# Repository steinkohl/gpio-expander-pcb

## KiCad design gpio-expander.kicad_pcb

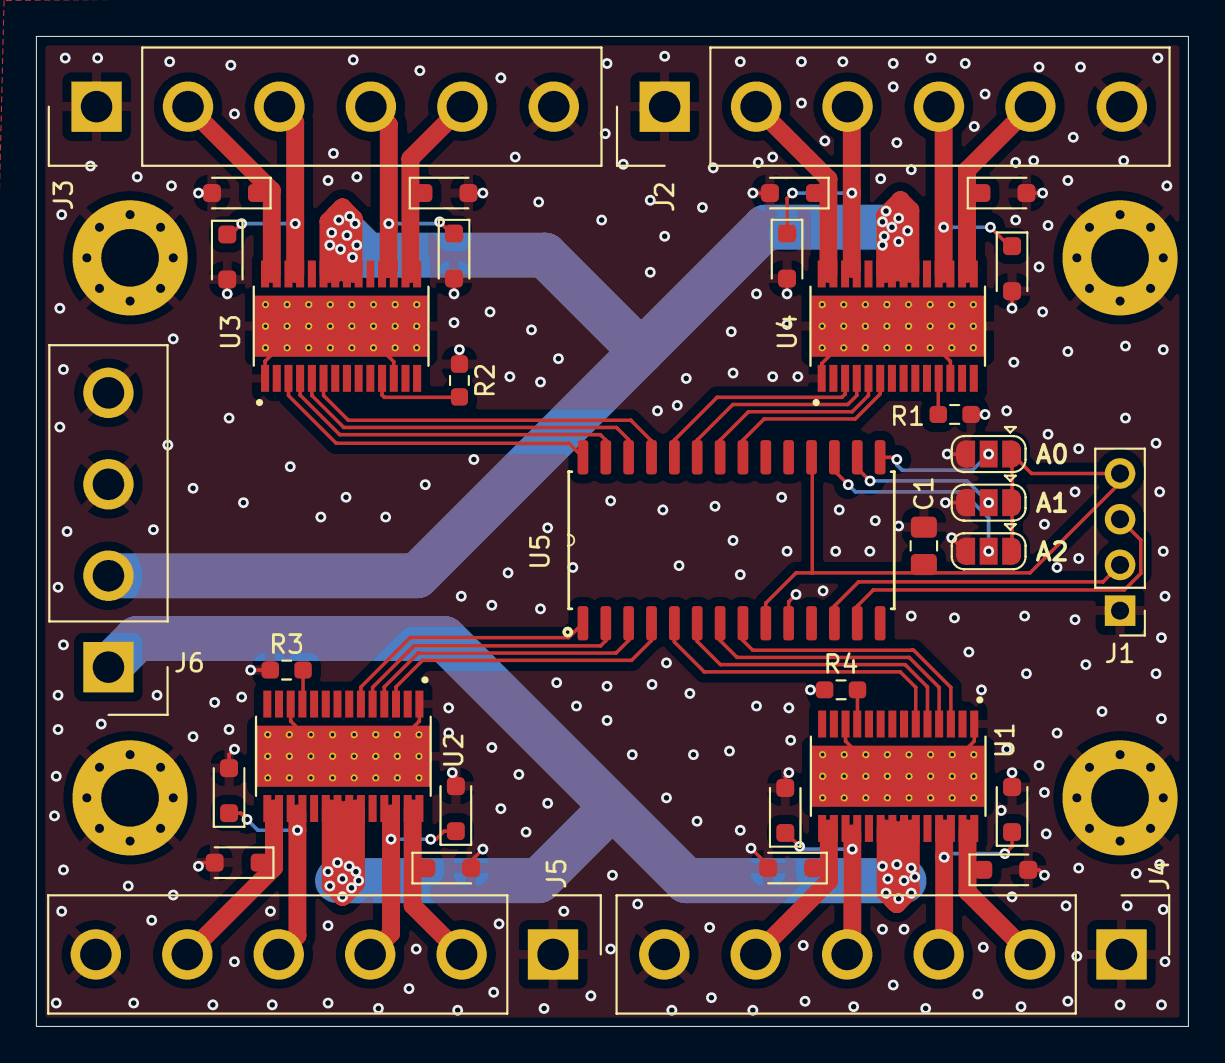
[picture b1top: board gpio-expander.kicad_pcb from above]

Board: 2 copper layers, 64.0 x 55.0 mm, 39 parts (0 on the bottom side), 44 nets.

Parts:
C1: C; C_0805_2012Metric_Pad1.18x1.45mm_HandSolder
D1, D2, D3, D4, D5, D6, D7, D8, D9, D10, D11, D12, D13, D14, D15, D16: 60V 1A; D_SOD-323_HandSoldering
H1, H2, H3, H4: MountingHole_Pad; MountingHole_3.2mm_M3_Pad_Via
J1: Conn_01x04; PinHeader_1x04_P2.54mm_Vertical
J2, J3, J4, J5: Conn_01x06; Samtec_HPM-06-05-x-S_Straight_1x06_Pitch5.08mm
J6: Conn_01x04; Samtec_HPM-04-05-x-S_Straight_1x04_Pitch5.08mm
JP1, JP2, JP3: SolderJumper_3_Open; SolderJumper-3_P1.3mm_Open_RoundedPad1.0x1.5mm
R1, R2, R3, R4: R; R_0603_1608Metric_Pad0.98x0.95mm_HandSolder
U1, U2, U3, U4: TPS4H160AQPWPRQ1; IC_TPS4H160AQPWPRQ1
U5: MCP23017T-E_SO; SOIC127P1030X265-28N

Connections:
+3V3: C1.1, J1.4, JP1.1 (A), JP2.1 (A), JP3.1 (A), U5.9 (VDD), U5.18 (~RESET)
+24V: J6.1, J6.2, U1.20 (VS), U1.21 (VS), U1.22 (VS), U1.23 (VS), U2.20 (VS), U2.21 (VS), U2.22 (VS), U2.23 (VS), U3.20 (VS), U3.21 (VS), U3.22 (VS), U3.23 (VS), U4.20 (VS), U4.21 (VS), U4.22 (VS), U4.23 (VS)
GND: C1.2, D1.2 (A), D2.2 (A), D3.2 (A), D4.2 (A), D5.2 (A), D6.2 (A), D7.2 (A), D8.2 (A), D9.2 (A), D10.2 (A), D11.2 (A), D12.2 (A), D13.2 (A), D14.2 (A), D15.2 (A), D16.2 (A), H1.1, H2.1, H3.1, H4.1, J1.1, J2.1, J2.6, J3.1, J3.6, J4.1, J4.6, J5.1, J5.6, J6.3, J6.4, JP1.3 (B), JP2.3 (B), JP3.3 (B), R1.1, R2.1, R3.1, R4.1, U1.1 (GND), U1.12 (GND), U1.29 (EXP), U1.30 (EXP), U1.31 (EXP), U1.32 (EXP), U1.33 (EXP), U1.34 (EXP), U1.35 (EXP), U1.36 (EXP), U1.37 (EXP), U1.38 (EXP), U1.39 (EXP), U1.40 (EXP), U1.41 (EXP), U1.42 (EXP), U1.43 (EXP), U1.44 (EXP), U1.45 (EXP), U1.46 (EXP), U1.47 (EXP), U1.48 (EXP), U1.49 (EXP), U1.50 (EXP), U1.51 (EXP), U1.52 (EXP), U1.53 (EXP), U2.1 (GND), U2.12 (GND), U2.29 (EXP), U2.30 (EXP), U2.31 (EXP), U2.32 (EXP), U2.33 (EXP), U2.34 (EXP), U2.35 (EXP), U2.36 (EXP), U2.37 (EXP), U2.38 (EXP), U2.39 (EXP), U2.40 (EXP), U2.41 (EXP), U2.42 (EXP), U2.43 (EXP), U2.44 (EXP), U2.45 (EXP), U2.46 (EXP), U2.47 (EXP), U2.48 (EXP), U2.49 (EXP), U2.50 (EXP), U2.51 (EXP), U2.52 (EXP), U2.53 (EXP), U3.1 (GND), U3.12 (GND), U3.29 (EXP), U3.30 (EXP), U3.31 (EXP), U3.32 (EXP), U3.33 (EXP), U3.34 (EXP), U3.35 (EXP), U3.36 (EXP), U3.37 (EXP), U3.38 (EXP), U3.39 (EXP), U3.40 (EXP), U3.41 (EXP), U3.42 (EXP), U3.43 (EXP), U3.44 (EXP), U3.45 (EXP), U3.46 (EXP), U3.47 (EXP), U3.48 (EXP), U3.49 (EXP), U3.50 (EXP), U3.51 (EXP), U3.52 (EXP), U3.53 (EXP), U4.1 (GND), U4.12 (GND), U4.29 (EXP), U4.30 (EXP), U4.31 (EXP), U4.32 (EXP), U4.33 (EXP), U4.34 (EXP), U4.35 (EXP), U4.36 (EXP), U4.37 (EXP), U4.38 (EXP), U4.39 (EXP), U4.40 (EXP), U4.41 (EXP), U4.42 (EXP), U4.43 (EXP), U4.44 (EXP), U4.45 (EXP), U4.46 (EXP), U4.47 (EXP), U4.48 (EXP), U4.49 (EXP), U4.50 (EXP), U4.51 (EXP), U4.52 (EXP), U4.53 (EXP), U5.10 (VSS)
unnamed: D1.1 (K), J3.2, U3.27 (OUT1), U3.28 (OUT1)
unnamed: D2.1 (K), J3.3, U3.25 (OUT2), U3.26 (OUT2)
unnamed: D3.1 (K), J3.4, U3.17 (OUT3), U3.18 (OUT3)
unnamed: D4.1 (K), J3.5, U3.15 (OUT4), U3.16 (OUT4)
unnamed: D5.1 (K), J2.5, U4.15 (OUT4), U4.16 (OUT4)
unnamed: D6.1 (K), J2.4, U4.17 (OUT3), U4.18 (OUT3)
unnamed: D7.1 (K), J2.3, U4.25 (OUT2), U4.26 (OUT2)
unnamed: D8.1 (K), J2.2, U4.27 (OUT1), U4.28 (OUT1)
unnamed: D9.1 (K), J4.2, U1.27 (OUT1), U1.28 (OUT1)
unnamed: D10.1 (K), J4.3, U1.25 (OUT2), U1.26 (OUT2)
unnamed: D11.1 (K), J4.4, U1.17 (OUT3), U1.18 (OUT3)
unnamed: D12.1 (K), J4.5, U1.15 (OUT4), U1.16 (OUT4)
unnamed: D13.1 (K), J5.2, U2.27 (OUT1), U2.28 (OUT1)
unnamed: D14.1 (K), J5.3, U2.25 (OUT2), U2.26 (OUT2)
unnamed: D15.1 (K), J5.4, U2.17 (OUT3), U2.18 (OUT3)
unnamed: D16.1 (K), J5.5, U2.15 (OUT4), U2.16 (OUT4)
unnamed: J1.2, U5.12 (SCK)
unnamed: J1.3, U5.13 (SDA)
unnamed: JP1.2 (C), U5.15 (A0)
unnamed: JP2.2 (C), U5.16 (A1)
unnamed: JP3.2 (C), U5.17 (A2)
unnamed: R4.2, U1.11 (CL)
unnamed: U1.3 (IN1), U5.8 (GPB7)
unnamed: U1.4 (IN2), U5.7 (GPB6)
unnamed: U1.5 (IN3), U5.6 (GPB5)
unnamed: U1.6 (IN4), U5.5 (GPB4)
unnamed: R3.2, U2.11 (CL)
unnamed: U2.3 (IN1), U5.4 (GPB3)
unnamed: U2.4 (IN2), U5.3 (GPB2)
unnamed: U2.5 (IN3), U5.2 (GPB1)
unnamed: U2.6 (IN4), U5.1 (GPB0)
unnamed: R2.2, U3.11 (CL)
unnamed: U3.3 (IN1), U5.28 (GPA7)
unnamed: U3.4 (IN2), U5.27 (GPA6)
unnamed: U3.5 (IN3), U5.26 (GPA5)
unnamed: U3.6 (IN4), U5.25 (GPA4)
unnamed: R1.2, U4.11 (CL)
unnamed: U4.3 (IN1), U5.24 (GPA3)
unnamed: U4.4 (IN2), U5.23 (GPA2)
unnamed: U4.5 (IN3), U5.22 (GPA1)
unnamed: U4.6 (IN4), U5.21 (GPA0)

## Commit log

2025-04-13 init
2025-05-26 added .gitignore
2025-05-26 first pcb revision
